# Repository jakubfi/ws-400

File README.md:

WS-400 is a device that connects to any of MERA-400 debug interfaces to display internal CPU and AWP states. You can see it in action [here](https://www.youtube.com/watch?v=3XAOpLWKt_o)

After powering the device on, user selects the debug interface which WS-400 is connected to with *SELECT* button. Available connections are:

* **CPU**: P-X (l), P-M (r), P-P (r), P-R (r), P-A (l),
* **AWP**: FPA (l) FPA (r), FPM (l), FPM (r), FPS (l).

Connector location (either left or right) is denoted in parentheses. Selection is confirmed with *OK* button and WS-400 immediately starts displaying active signals. If all active signals don't fit on the screen, right pointing arrow appears on the bottom right. *SELECT* button can then be used to switch to next portion of active signals.

User can also switch to raw display mode at any time with *OK* button. In this mode *SELECT* button allows switching between 16-bit portions of the interface view.

Device can also be installed on the interface rotated 180 degrees in Z axis. This requires translation of signal, which is achieved by powering on or resetting the device with button *OK* pressed.

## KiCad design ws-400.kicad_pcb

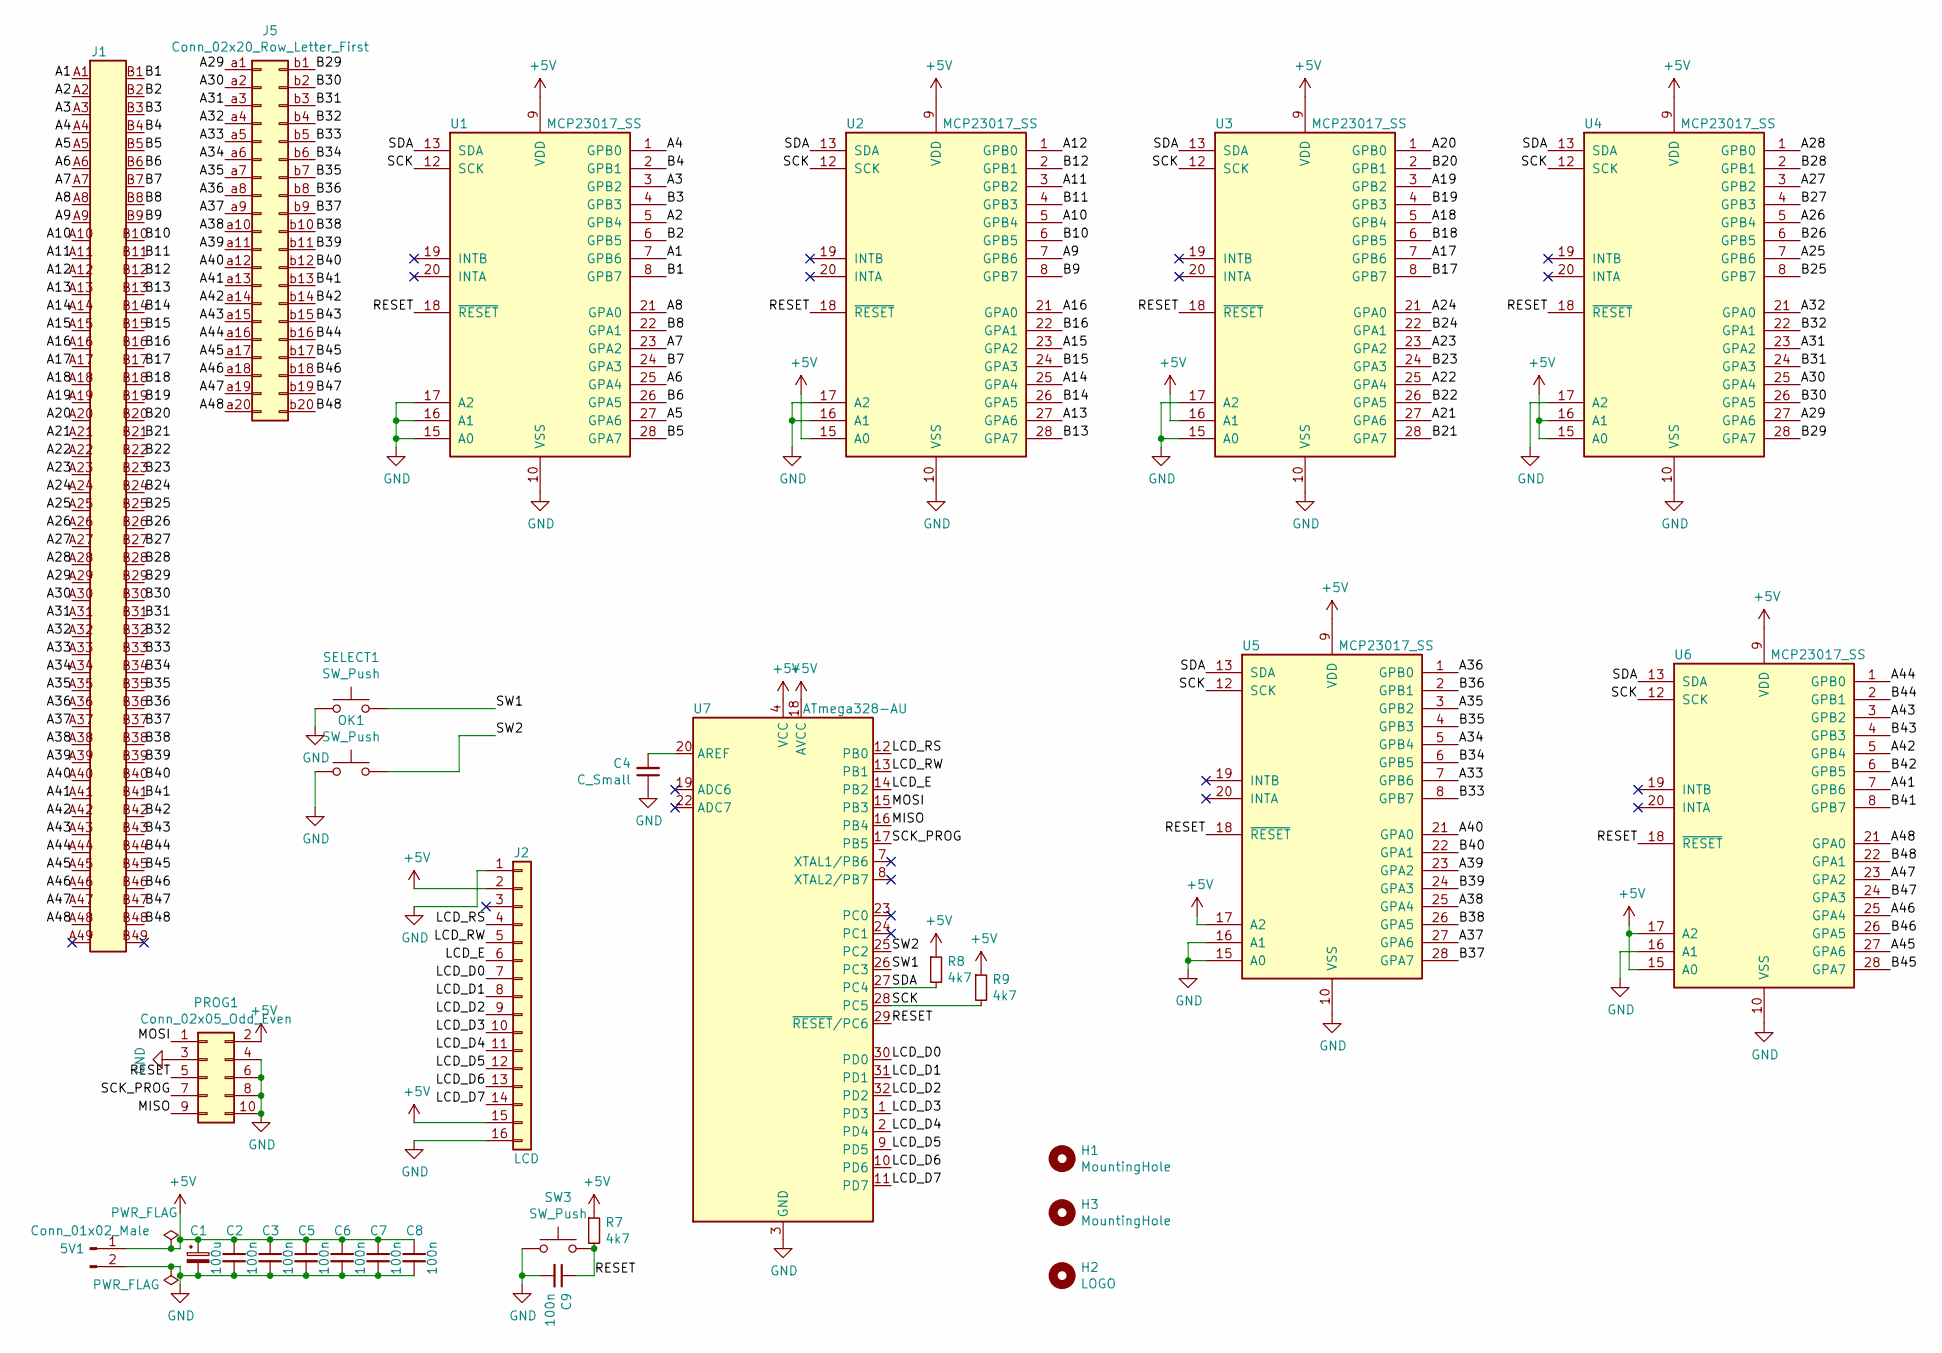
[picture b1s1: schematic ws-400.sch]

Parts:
5V1: Conn_01x02_Male; PinHeader_1x02_P2.54mm_Vertical
C1: 100u; CP_EIA-3528-21_Kemet-B_Pad1.50x2.35mm_HandSolder
C2, C3, C5, C6, C7, C8, C9: 100n; C_0805_2012Metric_Pad1.15x1.40mm_HandSolder
C4: C_Small; C_0805_2012Metric_Pad1.15x1.40mm_HandSolder
H1, H3: MountingHole; MountingHole_3mm
H2: LOGO; MERA400_LOGO_FCU_MEDIUM
J1: Conn_02x49; ELTRA801+
J2: LCD; PinHeader_1x16_P2.54mm_Vertical
J5: Conn_02x20_Row_Letter_First; 40pin_edge
OK1: SW_Push; SW_PUSH_6mm
PROG1: Conn_02x05_Odd_Even; PinHeader_2x05_P2.54mm_Vertical
R7, R8, R9: 4k7; R_0805_2012Metric_Pad1.15x1.40mm_HandSolder
SELECT1: SW_Push; SW_PUSH_6mm
SW3: SW_Push; SW_PUSH_6mm
U1, U2, U3, U4, U5, U6: MCP23017_SS; SSOP-28_5.3x10.2mm_P0.65mm
U7: ATmega328-AU; TQFP-32_7x7mm_P0.8mm

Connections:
+5V: 5V1.1, C1.1, C2.1, C3.1, C5.1, C6.1, C7.1, C8.1, J2.2, J2.15, PROG1.2, R7.1, R8.1, R9.1, U1.9 (VDD), U2.9 (VDD), U2.15 (A0), U3.9 (VDD), U3.16 (A1), U4.9 (VDD), U4.15 (A0), U4.16 (A1), U5.9 (VDD), U5.17 (A2), U6.9 (VDD), U6.15 (A0), U6.17 (A2), U7.4 (VCC), U7.6 (VCC), U7.18 (AVCC)
/A1: J1.A1, U1.7 (GPB6)
/A2: J1.A2, U1.5 (GPB4)
/A3: J1.A3, U1.3 (GPB2)
/A4: J1.A4, U1.1 (GPB0)
/A5: J1.A5, U1.27 (GPA6)
/A6: J1.A6, U1.25 (GPA4)
/A7: J1.A7, U1.23 (GPA2)
/A8: J1.A8, U1.21 (GPA0)
/A9: J1.A9, U2.7 (GPB6)
/A10: J1.A10, U2.5 (GPB4)
/A11: J1.A11, U2.3 (GPB2)
/A12: J1.A12, U2.1 (GPB0)
/A13: J1.A13, U2.27 (GPA6)
/A14: J1.A14, U2.25 (GPA4)
/A15: J1.A15, U2.23 (GPA2)
/A16: J1.A16, U2.21 (GPA0)
/A17: J1.A17, U3.7 (GPB6)
/A18: J1.A18, U3.5 (GPB4)
/A19: J1.A19, U3.3 (GPB2)
/A20: J1.A20, U3.1 (GPB0)
/A21: J1.A21, U3.27 (GPA6)
/A22: J1.A22, U3.25 (GPA4)
/A23: J1.A23, U3.23 (GPA2)
/A24: J1.A24, U3.21 (GPA0)
/A25: J1.A25, U4.7 (GPB6)
/A26: J1.A26, U4.5 (GPB4)
/A27: J1.A27, U4.3 (GPB2)
/A28: J1.A28, U4.1 (GPB0)
/A29: J1.A29, J5.a1, U4.27 (GPA6)
/A30: J1.A30, J5.a2, U4.25 (GPA4)
/A31: J1.A31, J5.a3, U4.23 (GPA2)
/A32: J1.A32, J5.a4, U4.21 (GPA0)
/A33: J1.A33, J5.a5, U5.7 (GPB6)
/A34: J1.A34, J5.a6, U5.5 (GPB4)
/A35: J1.A35, J5.a7, U5.3 (GPB2)
/A36: J1.A36, J5.a8, U5.1 (GPB0)
/A37: J1.A37, J5.a9, U5.27 (GPA6)
/A38: J1.A38, J5.a10, U5.25 (GPA4)
/A39: J1.A39, J5.a11, U5.23 (GPA2)
/A40: J1.A40, J5.a12, U5.21 (GPA0)
/A41: J1.A41, J5.a13, U6.7 (GPB6)
/A42: J1.A42, J5.a14, U6.5 (GPB4)
/A43: J1.A43, J5.a15, U6.3 (GPB2)
/A44: J1.A44, J5.a16, U6.1 (GPB0)
/A45: J1.A45, J5.a17, U6.27 (GPA6)
/A46: J1.A46, J5.a18, U6.25 (GPA4)
/A47: J1.A47, J5.a19, U6.23 (GPA2)
/A48: J1.A48, J5.a20, U6.21 (GPA0)
/B1: J1.B1, U1.8 (GPB7)
/B2: J1.B2, U1.6 (GPB5)
/B3: J1.B3, U1.4 (GPB3)
/B4: J1.B4, U1.2 (GPB1)
/B5: J1.B5, U1.28 (GPA7)
/B6: J1.B6, U1.26 (GPA5)
/B7: J1.B7, U1.24 (GPA3)
/B8: J1.B8, U1.22 (GPA1)
/B9: J1.B9, U2.8 (GPB7)
/B10: J1.B10, U2.6 (GPB5)
/B11: J1.B11, U2.4 (GPB3)
/B12: J1.B12, U2.2 (GPB1)
/B13: J1.B13, U2.28 (GPA7)
/B14: J1.B14, U2.26 (GPA5)
/B15: J1.B15, U2.24 (GPA3)
/B16: J1.B16, U2.22 (GPA1)
/B17: J1.B17, U3.8 (GPB7)
/B18: J1.B18, U3.6 (GPB5)
/B19: J1.B19, U3.4 (GPB3)
/B20: J1.B20, U3.2 (GPB1)
/B21: J1.B21, U3.28 (GPA7)
/B22: J1.B22, U3.26 (GPA5)
/B23: J1.B23, U3.24 (GPA3)
/B24: J1.B24, U3.22 (GPA1)
/B25: J1.B25, U4.8 (GPB7)
/B26: J1.B26, U4.6 (GPB5)
/B27: J1.B27, U4.4 (GPB3)
/B28: J1.B28, U4.2 (GPB1)
/B29: J1.B29, J5.b1, U4.28 (GPA7)
/B30: J1.B30, J5.b2, U4.26 (GPA5)
/B31: J1.B31, J5.b3, U4.24 (GPA3)
/B32: J1.B32, J5.b4, U4.22 (GPA1)
/B33: J1.B33, J5.b5, U5.8 (GPB7)
/B34: J1.B34, J5.b6, U5.6 (GPB5)
/B35: J1.B35, J5.b7, U5.4 (GPB3)
/B36: J1.B36, J5.b8, U5.2 (GPB1)
/B37: J1.B37, J5.b9, U5.28 (GPA7)
/B38: J1.B38, J5.b10, U5.26 (GPA5)
/B39: J1.B39, J5.b11, U5.24 (GPA3)
/B40: J1.B40, J5.b12, U5.22 (GPA1)
/B41: J1.B41, J5.b13, U6.8 (GPB7)
/B42: J1.B42, J5.b14, U6.6 (GPB5)
/B43: J1.B43, J5.b15, U6.4 (GPB3)
/B44: J1.B44, J5.b16, U6.2 (GPB1)
/B45: J1.B45, J5.b17, U6.28 (GPA7)
/B46: J1.B46, J5.b18, U6.26 (GPA5)
/B47: J1.B47, J5.b19, U6.24 (GPA3)
/B48: J1.B48, J5.b20, U6.22 (GPA1)
/LCD_D0: J2.7, U7.30 (PD0)
/LCD_D1: J2.8, U7.31 (PD1)
/LCD_D2: J2.9, U7.32 (PD2)
/LCD_D3: J2.10, U7.1 (PD3)
/LCD_D4: J2.11, U7.2 (PD4)
/LCD_D5: J2.12, U7.9 (PD5)
/LCD_D6: J2.13, U7.10 (PD6)
/LCD_D7: J2.14, U7.11 (PD7)
/LCD_E: J2.6, U7.14 (PB2)
/LCD_RS: J2.4, U7.12 (PB0)
/LCD_RW: J2.5, U7.13 (PB1)
/MISO: PROG1.9, U7.16 (PB4)
/MOSI: PROG1.1, U7.15 (PB3)
/RESET: C9.1, PROG1.5, R7.2, SW3.2, U1.18 (~RESET~), U2.18 (~RESET~), U3.18 (~RESET~), U4.18 (~RESET~), U5.18 (~RESET~), U6.18 (~RESET~), U7.29 (~RESET~/PC6)
/SCK: R9.2, U1.12 (SCK), U2.12 (SCK), U3.12 (SCK), U4.12 (SCK), U5.12 (SCK), U6.12 (SCK), U7.28 (PC5)
/SCK_PROG: PROG1.7, U7.17 (PB5)
/SDA: R8.2, U1.13 (SDA), U2.13 (SDA), U3.13 (SDA), U4.13 (SDA), U5.13 (SDA), U6.13 (SDA), U7.27 (PC4)
/SW1: SELECT1.2, U7.26 (PC3)
/SW2: OK1.2, U7.25 (PC2)
GND: 5V1.2, C1.2, C2.2, C3.2, C4.1, C5.2, C6.2, C7.2, C8.2, C9.2, J2.1, J2.16, OK1.1, PROG1.3, PROG1.4, PROG1.6, PROG1.8, PROG1.10, SELECT1.1, SW3.1, U1.10 (VSS), U1.15 (A0), U1.16 (A1), U1.17 (A2), U2.10 (VSS), U2.16 (A1), U2.17 (A2), U3.10 (VSS), U3.15 (A0), U3.17 (A2), U4.10 (VSS), U4.17 (A2), U5.10 (VSS), U5.15 (A0), U5.16 (A1), U6.10 (VSS), U6.16 (A1), U7.3 (GND), U7.5 (GND), U7.21 (GND)
unnamed: C4.2, U7.20 (AREF)

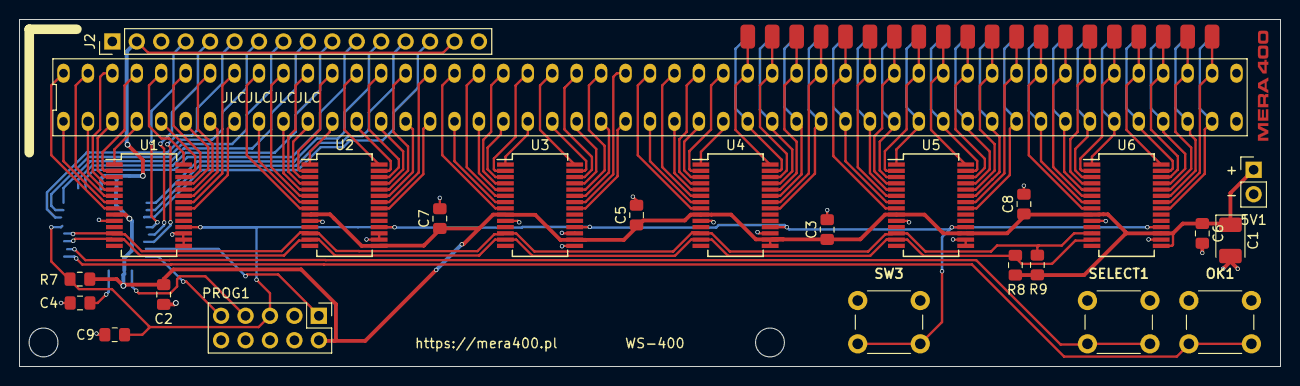
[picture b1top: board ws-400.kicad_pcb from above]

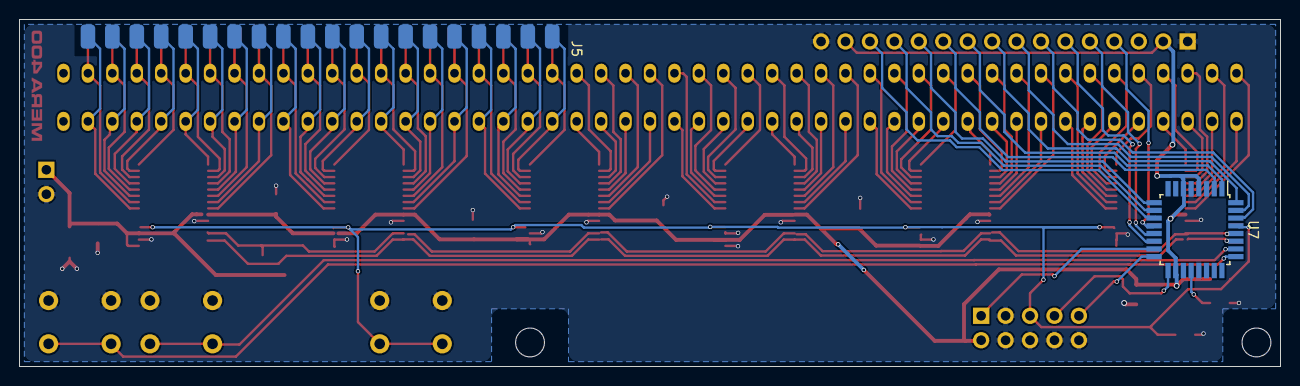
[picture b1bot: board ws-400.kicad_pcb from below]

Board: 2 copper layers, 131.1 x 36.1 mm, 30 parts (2 on the bottom side), 118 nets.

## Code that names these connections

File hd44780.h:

#ifndef __HD44780_H_
#define __HD44780_H_

#include <avr/io.h>

// --- port setup --------------------------------------------------------

#define LCD_RS_DIR	DDRB
#define LCD_RS_PORT	PORTB
#define LCD_RS		(1 << PB0)

#define LCD_RW_DIR	DDRB
#define LCD_RW_PORT	PORTB
#define LCD_RW		(1 << PB1)

#define LCD_E_DIR	DDRB
#define LCD_E_PORT	PORTB
#define LCD_E		(1 << PB2)

#define LCD_DATA_DIR	DDRD
#define LCD_DATA_PORT	PORTD
#define LCD_DATA_PIN	PIND

// --- HD44780 commands --------------------------------------------------

#define HD44780_CLEAR			0x01
#define HD44780_HOME			0x02
#define HD44780_ENTRY_MODE		0x04
#define HD44780_DISPLAY			0x08
#define HD44780_SHIFT			0x10
#define HD44780_FUNCTION		0x20
#define HD44780_CGRAM_ADDR		0x40
#define HD44780_DDRAM_ADDR		0x80

#define HD44780_EM_SHIFT_RIGHT	0 << 0
#define HD44780_EM_SHIFT_LEFT	1 << 0
#define HD44780_EM_NOSHIFT		0 << 1
#define HD44780_EM_SHIFT		1 << 1

#define HD44780_BLINK_OFF		0 << 0
#define HD44780_BLINK_ON		1 << 0
#define HD44780_CURSOR_OFF		0 << 1
#define HD44780_CURSOR_ON		1 << 1
#define HD44780_DISPLAY_OFF		0 << 2
#define HD44780_DISPLAY_ON		1 << 2

#define HD44780_SHIFT_LEFT		0 << 2
#define HD44780_SHIFT_RIGHT		1 << 2
#define HD44780_SHIFT_CURSOR	0 << 3
#define HD44780_SHIFT_DISPLAY	1 << 3

#define HD44780_FONT5x7			0 << 2
#define HD44780_FONT5x10		1 << 2
#define HD44780_ONE_LINE		0 << 3
#define HD44780_TWO_LINES		1 << 3
#define HD44780_4_BIT			0 << 4
#define HD44780_8_BIT			1 << 4

void lcd_write_cmd(const uint8_t cmd);
void lcd_write_data(const uint8_t data);
unsigned char lcd_read_data(void);
void lcd_puts(const char *str, int8_t len);
uint8_t lcd_print(const char *);
void lcd_setpos(const uint8_t x, const uint8_t y);
void lcd_clear(void);
void lcd_home(void);
void lcd_cg_set(const uint8_t ch, const __flash uint8_t *chdata);
void lcd_init(void);
uint8_t lcd_get_x();
uint8_t lcd_get_y();

#endif

// vim: tabstop=4 shiftwidth=4 autoindent

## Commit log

2020-07-13 dev and prod targets
2020-07-21 update pins and makefile for prod version
2020-07-22 fix mcp23017 addressing
2020-07-22 move stuff to __flash
2020-07-22 much rework
2020-07-23 mostly working
2020-07-23 raw order OK
2020-07-23 raw print fixes
2020-07-23 neg dec display
2020-07-24 separate scr.{h,c}
2020-07-24 janitorial
2020-07-24 wait for key depress after conn select
2020-12-30 fixes:
    * shift partial decimal values
    * swap FPA/FPM
    * fix FIC order
2021-09-19 build fix
2021-09-19 comments, refactor
2021-09-19 use one blit
2021-09-19 separate check_rotation()
2021-09-20 better key management
2021-09-20 update screen only if needed
2021-09-20 pins rework
    * introduce pin attributes
    * simplify print type selection logic
    * fix some pins polarity
    * add missinf pins
2021-09-20 style fix
2021-09-21 fill bus data only if signals change
2021-09-21 make print_raw() work again
2021-09-22 rework signal mapping logic
2021-09-22 fix FIC2 shift
2021-09-22 compact pin tables by unionizing fields, fix register terminators
2021-09-22 bigger string buffer
2021-09-22 add Kicad files
2021-09-22 schematic cleanup
2021-09-22 add image
2021-09-22 added readme
